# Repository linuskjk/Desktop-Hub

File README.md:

# Desktop Hub

What this project is
--------------------
This project is a compact desktop USB 2.0 hub built around the GL852G hub controller. It gives you:
- One USB-C upstream port (to connect to a host)
- Two USB-A downstream ports plus one USB-C downstream port
- Per-port power switches (TPS2051C) to protect and limit current to each downstream port
- ESD protection on USB data and power lines

Why I want to build it   I-
----------------------
- Want a small, DIY USB hub for flash drives, keyboards, mice, and low-power peripherals
- Need a hub you can modify (change ESD parts, use different power switches, or tweak traces for higher current)
- Learn about hub controllers, USB signal routing, and SMD assembly

Quick features and limits
-------------------------
- USB 2.0 data speeds supported (Full Speed/High Speed up to USB 2.0 limits)
- Signal traces for D+/D− are routed at 0.2 mm (fine and short — good for USB 2.0)
- VBUS/GND are routed at 0.2 mm in this version due to spacing problems— suitable for flash drives and low-current devices; phone charging will be limited

Licensing
---------
This project is released under the MIT License.

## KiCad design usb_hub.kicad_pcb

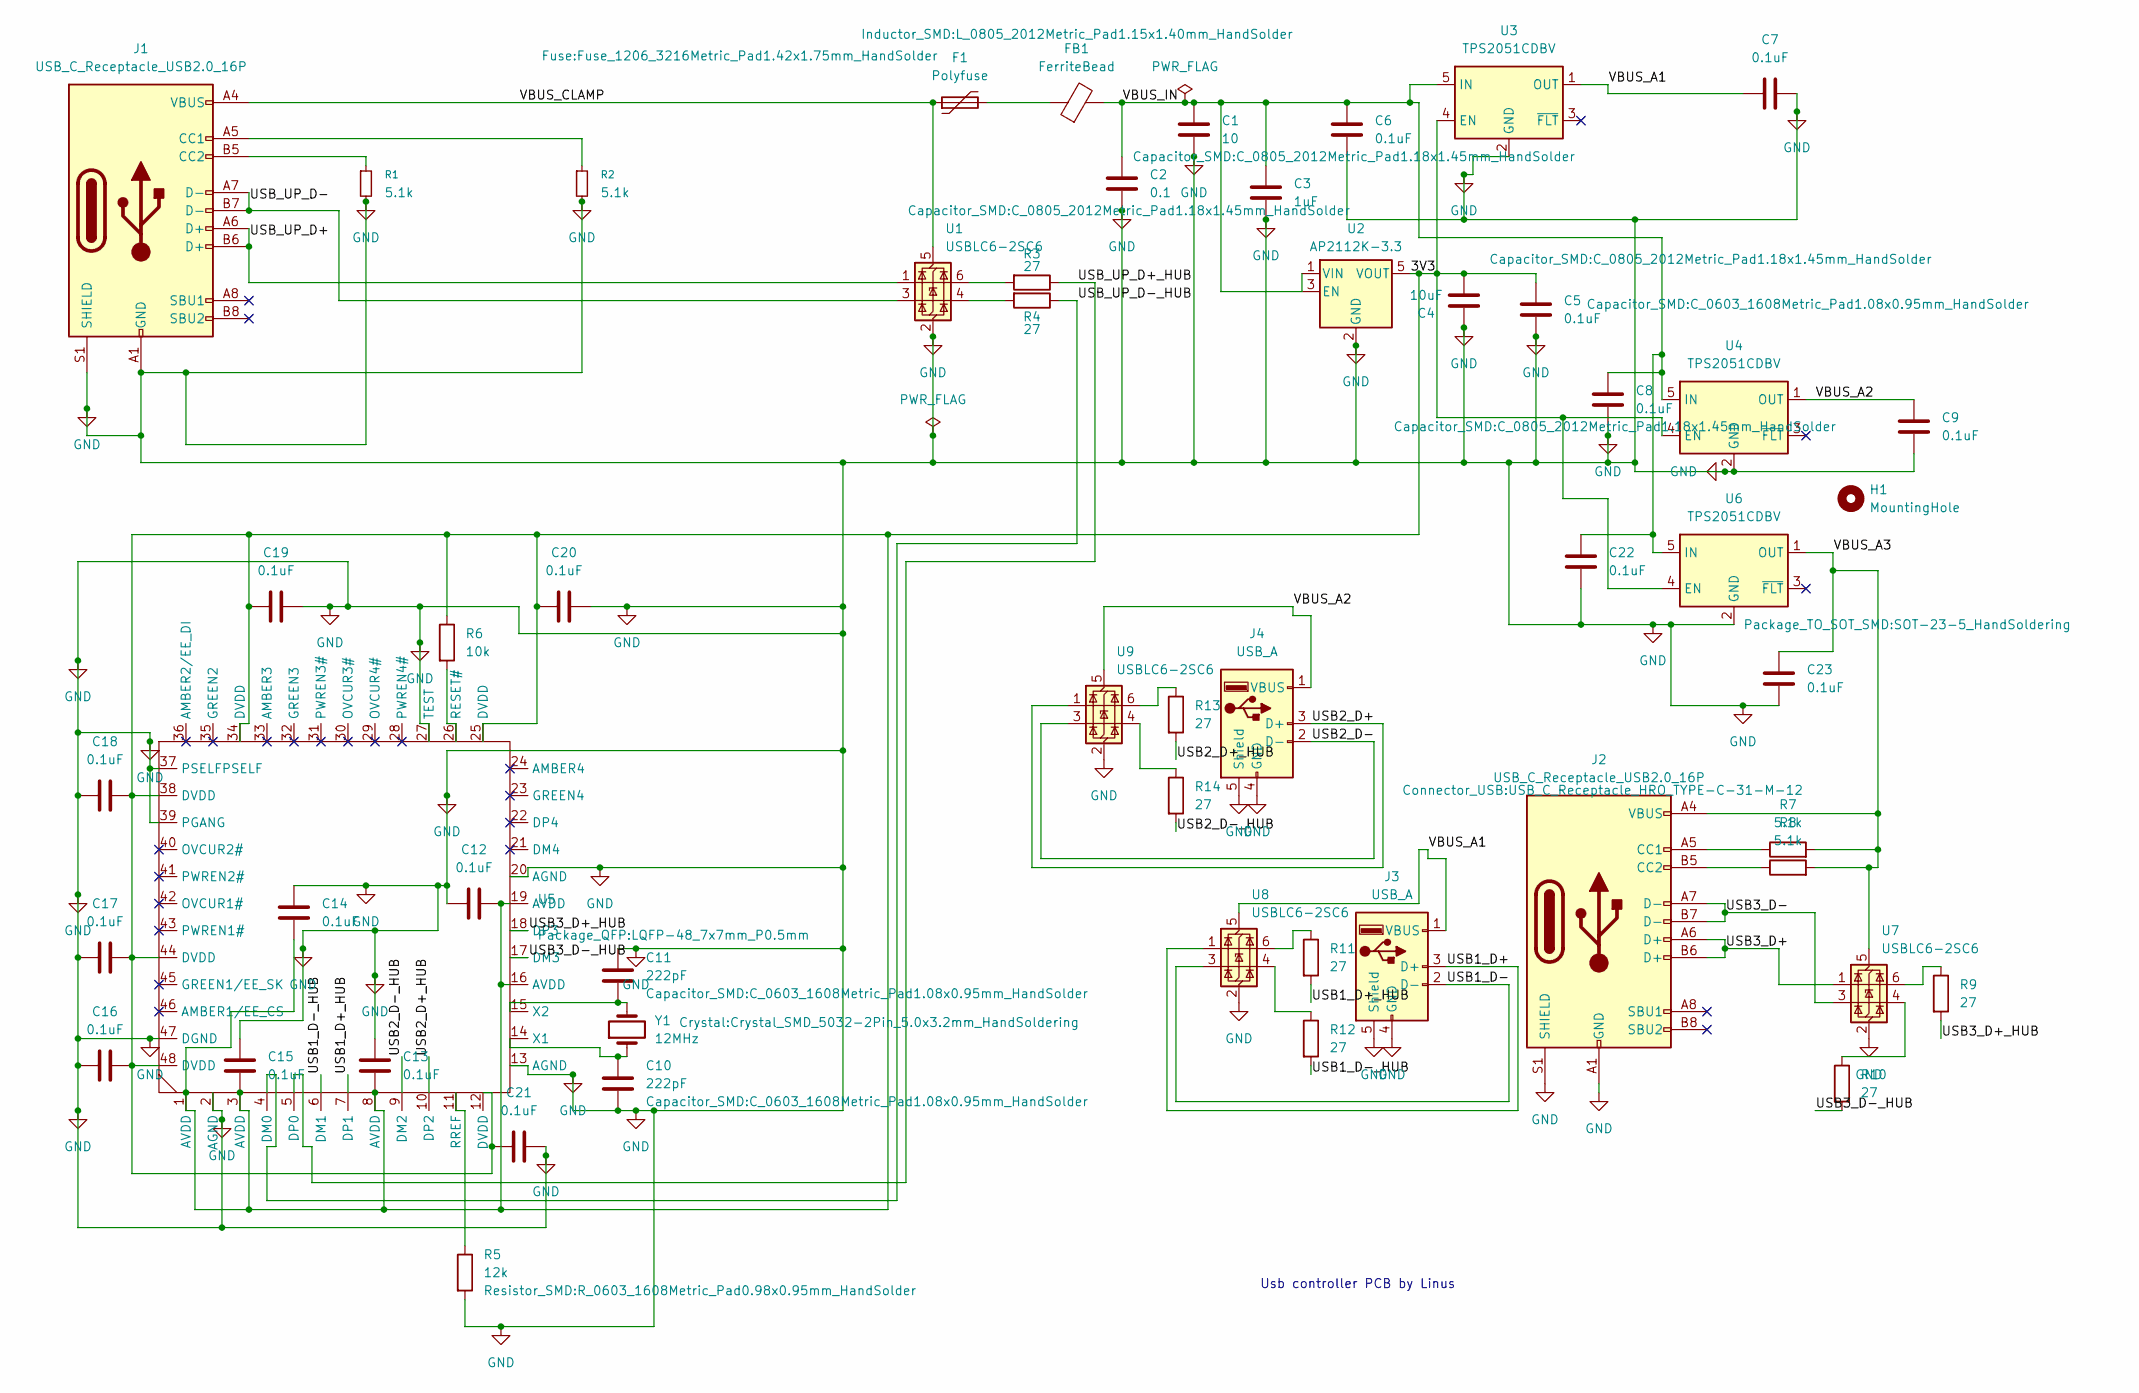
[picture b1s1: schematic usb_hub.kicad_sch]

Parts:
C1: 10; C_0805_2012Metric_Pad1.18x1.45mm_HandSolder
C2: 0.1; C_0805_2012Metric_Pad1.18x1.45mm_HandSolder
C3: 1uF; C_0603_1608Metric_Pad1.08x0.95mm_HandSolder
C4: 10uF; C_0805_2012Metric_Pad1.18x1.45mm_HandSolder
C5, C7, C9, C12, C13, C14, C15, C16, C17, C18, C19, C20, C21, C22, C23: 0.1uF; C_0603_1608Metric_Pad1.08x0.95mm_HandSolder
C6, C8: 0.1uF; C_0805_2012Metric_Pad1.18x1.45mm_HandSolder
C10, C11: 222pF; C_0603_1608Metric_Pad1.08x0.95mm_HandSolder
F1: Polyfuse; Fuse_1206_3216Metric_Pad1.42x1.75mm_HandSolder
FB1: FerriteBead; L_0805_2012Metric_Pad1.15x1.40mm_HandSolder
H1: MountingHole
J1, J2: USB_C_Receptacle_USB2.0_16P; USB_C_Receptacle_HRO_TYPE-C-31-M-12
J3, J4: USB_A; USB_A_Stewart_SS-52100-001_Horizontal
R1, R2, R7, R8: 5.1k; R_0603_1608Metric_Pad0.98x0.95mm_HandSolder
R3, R4, R9, R10, R11, R12, R13, R14: 27; R_0603_1608Metric_Pad0.98x0.95mm_HandSolder
R5: 12k; R_0603_1608Metric_Pad0.98x0.95mm_HandSolder
R6: 10k; R_0603_1608Metric_Pad0.98x0.95mm_HandSolder
U1, U7, U8, U9: USBLC6-2SC6; SOT-23-6
U2: AP2112K-3.3; SOT-23-5
U3, U4: TPS2051CDBV; SOT-23-5
U5: LQFP-48_7x7mm_P0.5mm
U6: TPS2051CDBV; SOT-23-5_HandSoldering
Y1: 12MHz; Crystal_SMD_5032-2Pin_5.0x3.2mm_HandSoldering

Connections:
/3V3: C4.2, C5.1, C12.2, C13.1, C14.1, C15.1, C16.2, C17.2, C18.2, C19.2, C20.1, C21.1, R6.1, U2.5 (VOUT), U3.4 (EN), U4.4 (EN), U5.1 (AVDD), U5.3 (AVDD), U5.8 (AVDD), U5.12 (DVDD), U5.16 (AVDD), U5.19 (AVDD), U5.25 (DVDD), U5.34 (DVDD), U5.38 (DVDD), U5.44 (DVDD), U5.48 (DVDD), U6.4 (EN)
/USB1_D+: J3.3 (D+), U8.1 (I/O1)
/USB1_D+_HUB: R11.2, U5.7 (DP1)
/USB1_D-: J3.2 (D-), U8.3 (I/O2)
/USB1_D-_HUB: R12.2, U5.6 (DM1)
/USB2_D+: J4.3 (D+), U9.1 (I/O1)
/USB2_D+_HUB: R13.2, U5.10 (DP2)
/USB2_D-: J4.2 (D-), U9.3 (I/O2)
/USB2_D-_HUB: R14.2, U5.9 (DM2)
/USB3_D+: J2.A6 (D+), J2.B6 (D+), U7.1 (I/O1)
/USB3_D+_HUB: R9.2, U5.18 (DP3)
/USB3_D-: J2.A7 (D-), J2.B7 (D-), U7.3 (I/O2)
/USB3_D-_HUB: R10.2, U5.17 (DM3)
/USB_UP_D+: J1.A6 (D+), J1.B6 (D+), U1.1 (I/O1)
/USB_UP_D+_HUB: R3.1, U5.5 (DP0)
/USB_UP_D-: J1.A7 (D-), J1.B7 (D-), U1.3 (I/O2)
/USB_UP_D-_HUB: R4.1, U5.4 (DM0)
/VBUS_A1: C7.2, J3.1 (VBUS), U3.1 (OUT), U8.5 (VBUS)
/VBUS_A2: C9.2, J4.1 (VBUS), U4.1 (OUT), U9.5 (VBUS)
/VBUS_A3: C23.1, J2.A4 (VBUS), J2.A9 (VBUS), J2.B4 (VBUS), J2.B9 (VBUS), R7.2, R8.2, U6.1 (OUT), U7.5 (VBUS)
/VBUS_CLAMP: F1.1, J1.A4 (VBUS), J1.A9 (VBUS), J1.B4 (VBUS), J1.B9 (VBUS), U1.5 (VBUS)
/VBUS_IN: C1.2, C2.1, C3.1, C6.1, C8.1, C22.1, FB1.2, U2.1 (VIN), U2.3 (EN), U3.5 (IN), U4.5 (IN), U6.5 (IN)
GND: C1.1, C2.2, C3.2, C4.1, C5.2, C6.2, C7.1, C8.2, C9.1, C10.2, C11.1, C12.1, C13.2, C14.2, C15.2, C16.1, C17.1, C18.1, C19.1, C20.2, C21.2, C22.2, C23.2, J1.A1 (GND), J1.A12 (GND), J1.B1 (GND), J1.B12 (GND), J1.S1 (SHIELD), J2.A1 (GND), J2.A12 (GND), J2.B1 (GND), J2.B12 (GND), J2.S1 (SHIELD), J3.4 (GND), J3.5 (Shield), J4.4 (GND), J4.5 (Shield), R1.2, R2.2, R5.2, U1.2 (GND), U2.2 (GND), U3.2 (GND), U4.2 (GND), U5.2 (AGND), U5.13 (AGND), U5.20 (AGND), U5.27 (TEST), U5.37 (PSELFPSELF), U5.39 (PGANG), U5.47 (DGND), U6.2 (GND), U7.2 (GND), U8.2 (GND), U9.2 (GND)
unnamed: F1.2, FB1.1
unnamed: J1.A5 (CC1), R2.1
unnamed: J1.B5 (CC2), R1.1
unnamed: J2.A5 (CC1), R7.1
unnamed: J2.B5 (CC2), R8.1
unnamed: R3.2, U1.6 (I/O1)
unnamed: R4.2, U1.4 (I/O2)
unnamed: R9.1, U7.6 (I/O1)
unnamed: R10.1, U7.4 (I/O2)
unnamed: R11.1, U8.6 (I/O1)
unnamed: R12.1, U8.4 (I/O2)
unnamed: R13.1, U9.6 (I/O1)
unnamed: R14.1, U9.4 (I/O2)
unnamed: R6.2, U5.26 (RESET#)
unnamed: R5.1, U5.11 (RREF)
unnamed: C10.1, U5.14 (X1), Y1.1
unnamed: C11.2, U5.15 (X2), Y1.2

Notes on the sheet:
Usb controller PCB by Linus

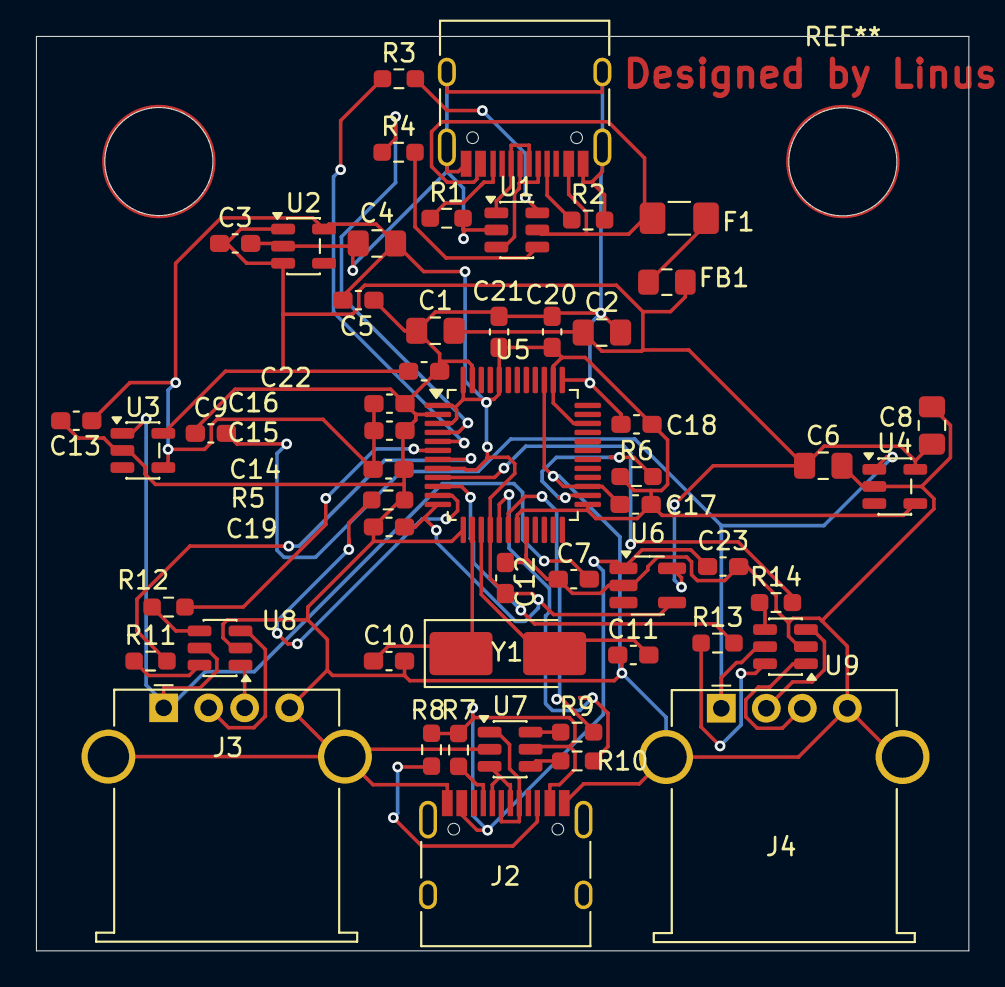
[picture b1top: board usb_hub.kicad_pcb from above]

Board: 2 copper layers, 51.8 x 50.8 mm, 53 parts (0 on the bottom side), 40 nets.

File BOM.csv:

Reference,Qty,Value / Description,DNP,Exclude from BOM,Exclude from Board,Footprint,Datasheet,Notes
C1,1,10uF,, , ,Capacitor_SMD:C_0805_2012Metric_Pad1.18x1.45mm_HandSolder,~,As on schematic
C2,1,0.1uF,, , ,Capacitor_SMD:C_0805_2012Metric_Pad1.18x1.45mm_HandSolder,~,As on schematic
C3,1,1uF,, , ,Capacitor_SMD:C_0603_1608Metric_Pad1.08x0.95mm_HandSolder,~,As on schematic
C4,1,10uF,, , ,Capacitor_SMD:C_0805_2012Metric_Pad1.18x1.45mm_HandSolder,~,As on schematic
"C5,C7,C9,C12,C13,C14,C15,C16,C17,C18,C19,C20,C21,C22,C23",15,0.1uF,, , ,Capacitor_SMD:C_0603_1608Metric_Pad1.08x0.95mm_HandSolder,~,Bulk decoupling
"C6,C8",2,0.1uF,, , ,Capacitor_SMD:C_0805_2012Metric_Pad1.18x1.45mm_HandSolder,~,As on schematic
"C10,C11",2,222pF,, , ,Capacitor_SMD:C_0603_1608Metric_Pad1.08x0.95mm_HandSolder,~,Crystal loading
F1,1,Polyfuse 1206,, , ,Fuse:Fuse_1206_3216Metric_Pad1.42x1.75mm_HandSolder,~,VBUS overcurrent protection
FB1,1,Ferrite Bead 0805,, , ,Inductor_SMD:L_0805_2012Metric_Pad1.15x1.40mm_HandSolder,~,EMI on VBUS
H1,1,MountingHole,,Excluded from BOM, , , ,Mechanical hole (NPTH)
"J1,J2",2,USB_C_Receptacle_USB2.0_16P,, , ,Connector_USB:USB_C_Receptacle_HRO_TYPE-C-31-M-12,https://www.usb.org/sites/default/files/documents/usb_type-c.zip,Upstream and downstream USB-C
"J3,J4",2,USB_A,, , ,Connector_USB:USB_A_Stewart_SS-52100-001_Horizontal,~,USB-A downstream ports
"R1,R2,R7,R8",4,5.1k,, , ,Resistor_SMD:R_0603_1608Metric_Pad0.98x0.95mm_HandSolder,~,Pull-downs/dividers
"R3,R4,R9,R10,R11,R12,R13,R14",8,27,, , ,Resistor_SMD:R_0603_1608Metric_Pad0.98x0.95mm_HandSolder,~,Pull-downs
R5,1,12k,, , ,Resistor_SMD:R_0603_1608Metric_Pad0.98x0.95mm_HandSolder,~,Net resistors
R6,1,10k,, , ,Resistor_SMD:R_0603_1608Metric_Pad0.98x0.95mm_HandSolder,~,Pull-up
"U1,U7,U8,U9",4,USBLC6-2SC6 (ESD Diode),, , ,Package_TO_SOT_SMD:SOT-23-6,https://www.st.com/resource/en/datasheet/usblc6-2.pdf,USB ESD protection
U2,1,AP2112K-3.3 (LDO),, , ,Package_TO_SOT_SMD:SOT-23-5,https://www.diodes.com/assets/Datasheets/AP2112.pdf,3.3V regulator
"U3,U4",2,TPS2051CDBV (USB power switch),, , ,Package_TO_SOT_SMD:SOT-23-5,https://www.ti.com/lit/ds/symlink/tps2051c.pdf,Per-port power switch
U5,1,GL852G (LQFP-48) hub controller,, , ,Package_QFP:LQFP-48_7x7mm_P0.5mm,,Verify footprint and paste
U6,1,TPS2051CDBV (USB power switch),, , ,Package_TO_SOT_SMD:SOT-23-5_HandSoldering,https://www.ti.com/lit/ds/symlink/tps2051c.pdf,Per-port power switch
Y1,1,12MHz Crystal 5032,, , ,Crystal:Crystal_SMD_5032-2Pin_5.0x3.2mm_HandSoldering,~,Hub clock

# Additional non-PCB items and accessories (not mounted on PCB)
USB-C upstream cable,1,USB-C to USB-A (or C-to-C) cable, ,Exclude from BOM, ,Cable,~,Use appropriate cable for host connection (choose C-to-C for modern hosts)
MagSafe adapter (external),1,Apple MagSafe adapter or magnetic power adapter (optional),,Exclude from BOM, ,Accessory,~,Optional external magnetic power adapter; verify model compatibility – not a PCB part
5V DC power adapter (optional),1,5V 2A power supply (if using external power),,Exclude from BOM, ,Accessory,~,Optional external power supply for VBUS when used standalone
